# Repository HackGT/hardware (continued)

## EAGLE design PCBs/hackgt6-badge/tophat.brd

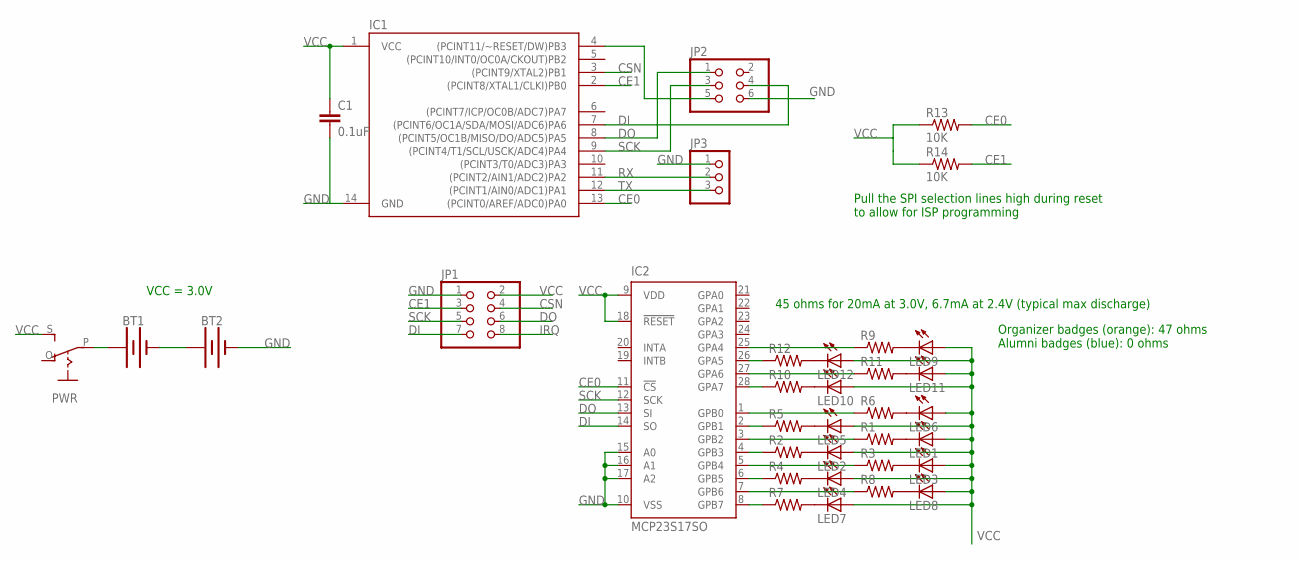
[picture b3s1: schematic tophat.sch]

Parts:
BT1, BT2: BATTERY-AA-SMD
C1: 0.1uF; C1206
IC1: ATTINY84; SO14
IC2: MCP23S17SO; SO28W
JP1: PINHD-2X4/90; 2X04/90
JP2: PINHD-2X3; 2X03
JP3: PINHD-1X3; 1X03
LED1, LED2, LED3, LED4, LED5, LED6, LED7, LED8, LED9, LED10, LED11, LED12: LEDSMT1206; 1206
PWR: EG1218S; EG1218
R1, R2, R3, R4, R5, R6, R7, R8, R9, R10, R11, R12: R-US_R1206; R1206
R13, R14: 10K; R1206

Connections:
CE0: IC1.13 ((PCINT0/AREF/ADC0)PA0), IC2.11 (!CS), R13.2
CE1: IC1.2 ((PCINT8/XTAL1/CLKI)PB0), JP1.3, R14.2
CSN: IC1.3 ((PCINT9/XTAL2)PB1), JP1.4
DI: IC1.7 ((PCINT6/OC1A/SDA/MOSI/ADC6)PA6), IC2.14 (SO), JP1.7, JP2.4
DO: IC1.8 ((PCINT5/OC1B/MISO/DO/ADC5)PA5), IC2.13 (SI), JP1.6, JP2.1
GND: BT2.P$2 (-), BT2.P$4 (-), C1.2, IC1.14 (GND), IC2.10 (VSS), IC2.15 (A0), IC2.16 (A1), IC2.17 (A2), JP1.1, JP2.6, JP3.1
IRQ: JP1.8
unnamed: BT1.P$2 (-), BT1.P$4 (-), BT2.P$1 (+), BT2.P$3 (+)
unnamed: BT1.P$1 (+), BT1.P$3 (+), PWR.P
unnamed: IC2.28 (GPA7), R10.1
unnamed: IC2.27 (GPA6), R11.1
unnamed: LED1.C, R1.2
unnamed: LED2.C, R2.2
unnamed: LED3.C, R3.2
unnamed: LED4.C, R4.2
unnamed: LED5.C, R5.2
unnamed: LED6.C, R6.2
unnamed: LED7.C, R7.2
unnamed: LED8.C, R8.2
unnamed: IC2.26 (GPA5), R12.1
unnamed: IC2.25 (GPA4), R9.1
unnamed: IC2.8 (GPB7), R7.1
unnamed: IC2.1 (GPB0), R6.1
unnamed: IC2.2 (GPB1), R5.1
unnamed: IC2.3 (GPB2), R1.1
unnamed: IC2.4 (GPB3), R2.1
unnamed: IC2.5 (GPB4), R3.1
unnamed: IC2.6 (GPB5), R4.1
unnamed: IC2.7 (GPB6), R8.1
unnamed: LED9.C, R9.2
unnamed: LED10.C, R10.2
unnamed: LED11.C, R11.2
unnamed: LED12.C, R12.2
RST: IC1.4 ((PCINT11/~RESET/DW)PB3), JP2.5
RX: IC1.11 ((PCINT2/AIN1/ADC2)PA2), JP3.2
SCK: IC1.9 ((PCINT4/T1/SCL/USCK/ADC4)PA4), IC2.12 (SCK), JP1.5, JP2.3
TX: IC1.12 ((PCINT1/AIN0/ADC1)PA1), JP3.3
VCC: C1.1, IC1.1 (VCC), IC2.9 (VDD), IC2.18 (!RESET), JP1.2, LED1.A, LED2.A, LED3.A, LED4.A, LED5.A, LED6.A, LED7.A, LED8.A, LED9.A, LED10.A, LED11.A, LED12.A, PWR.S, R13.1, R14.1

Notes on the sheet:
VCC = 3.0V
45 ohms for 20mA at 3.0V, 6.7mA at 2.4V (typical max discharge)
Organizer badges (orange): 47 ohms Alumni badges (blue): 0 ohms
Pull the SPI selection lines high during reset to allow for ISP programming

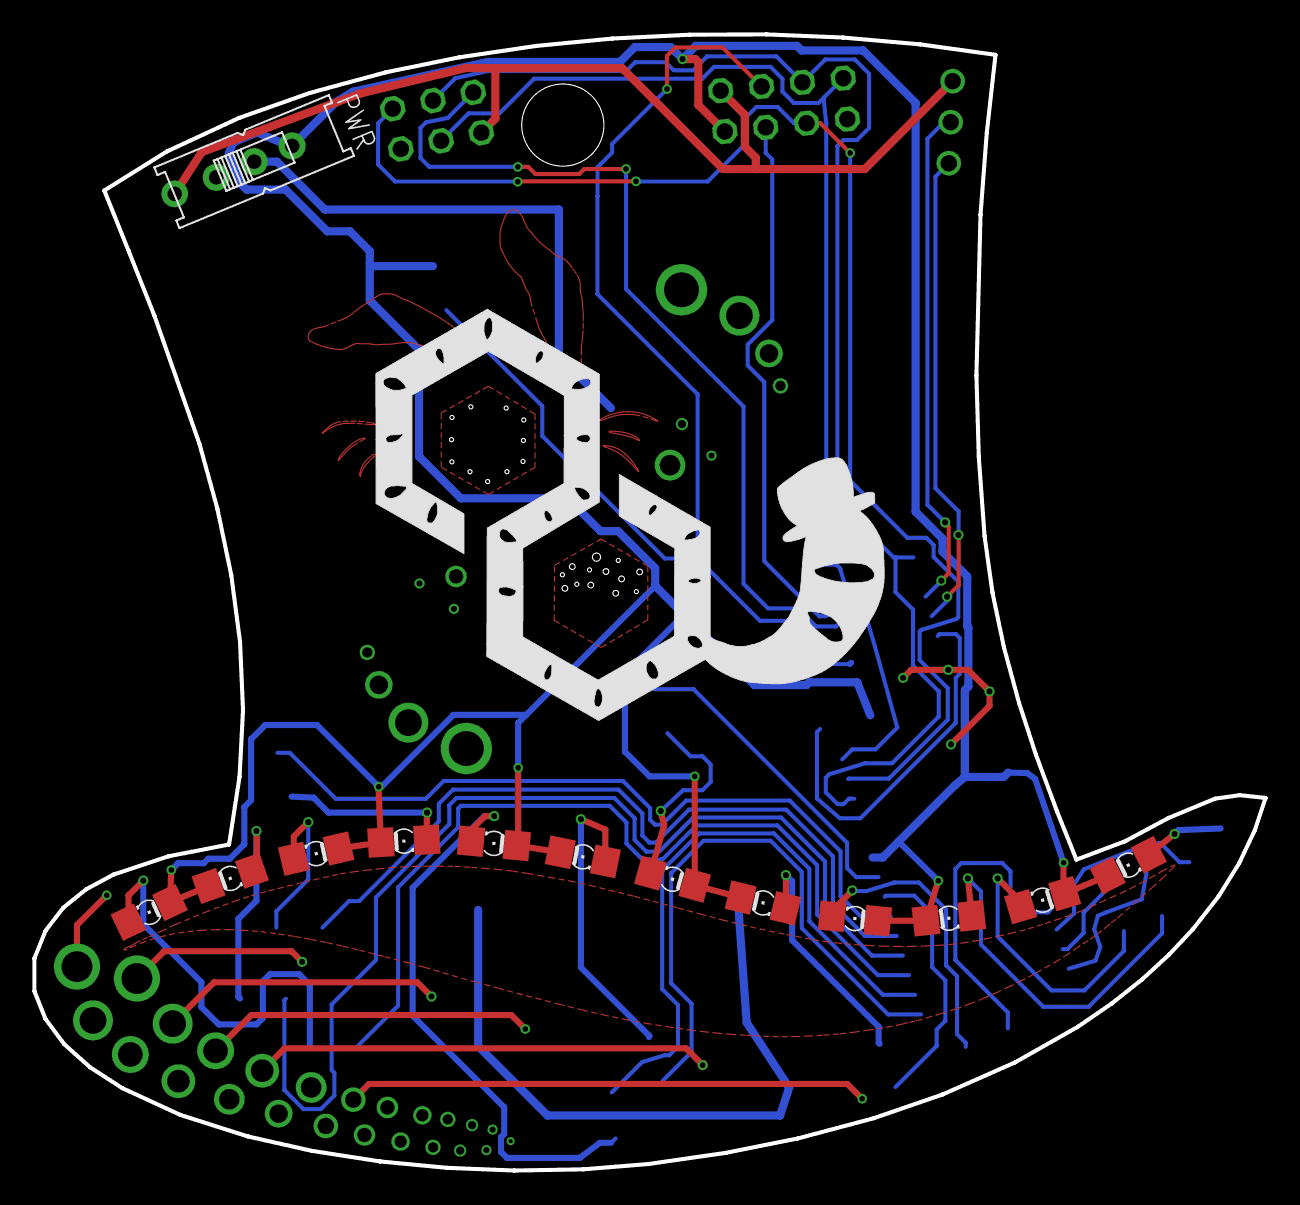
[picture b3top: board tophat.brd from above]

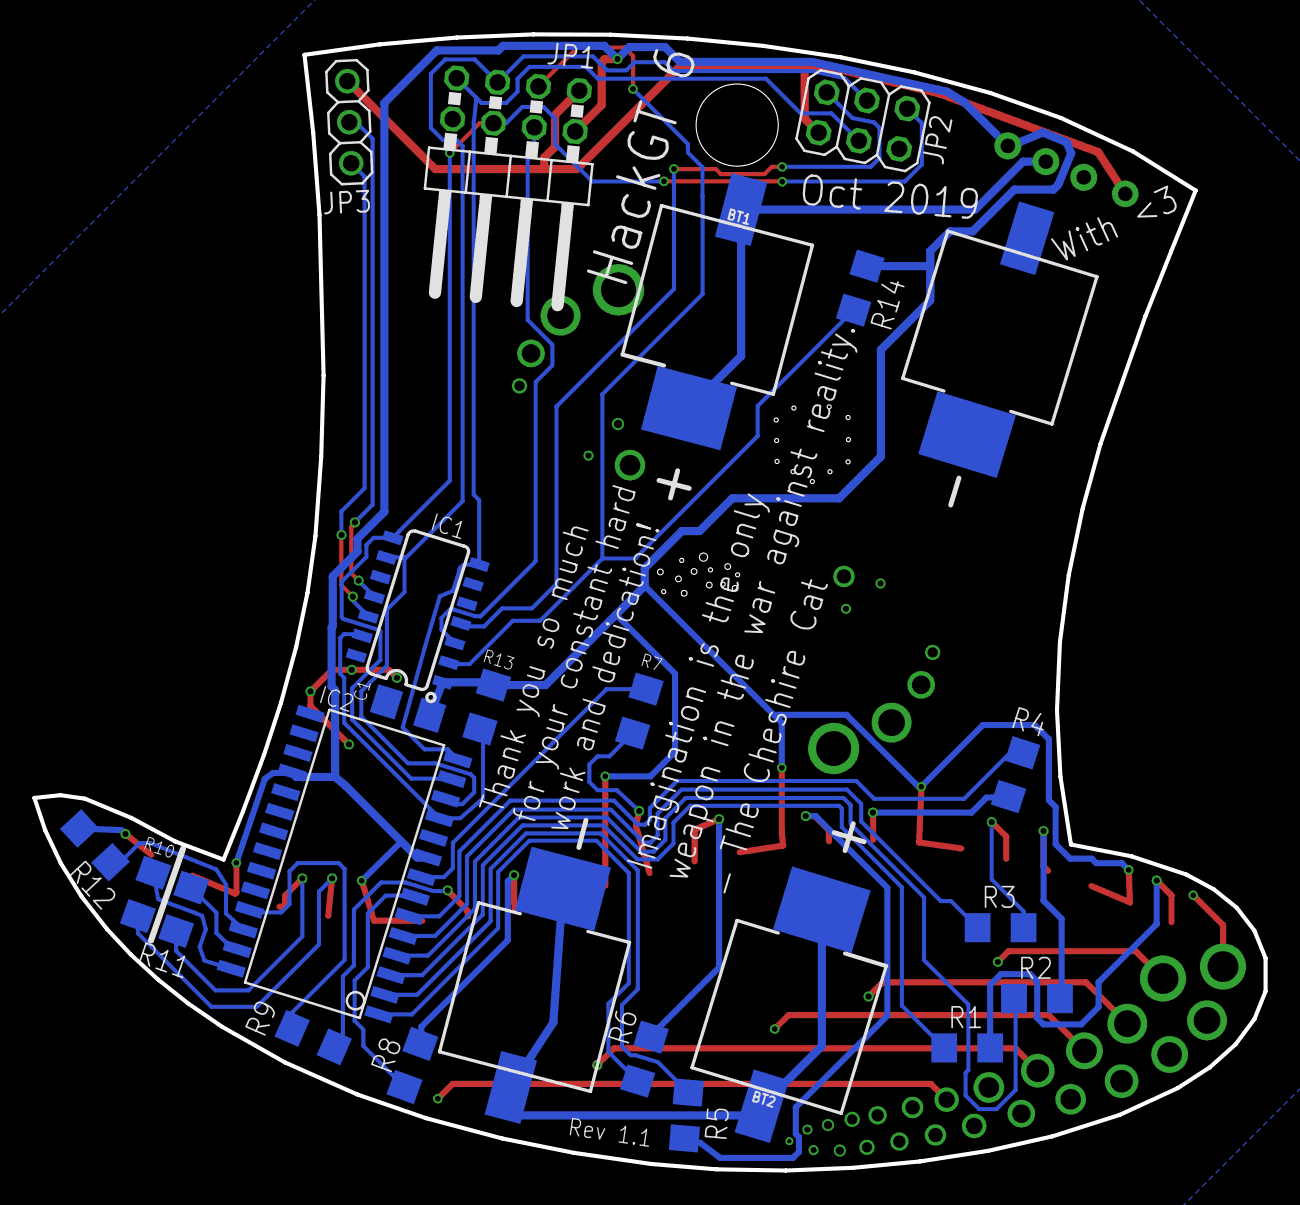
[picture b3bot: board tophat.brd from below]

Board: 2 copper layers, 76.1 x 70.3 mm, 35 parts (22 on the bottom side), 37 nets.

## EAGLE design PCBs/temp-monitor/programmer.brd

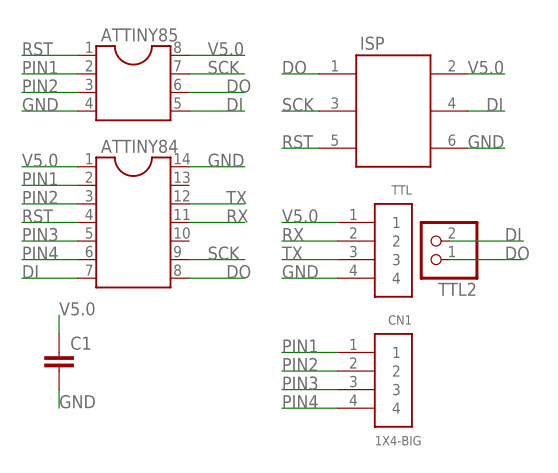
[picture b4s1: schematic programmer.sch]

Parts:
ATTINY84: DIL14S; SOCKET-14
ATTINY85: DIL8S; SOCKET-08
C1: C-EU025-025X050; C025-025X050
CN1: 1X4-BIG; 1X04-BIG
ISP: 61200621621
TTL: 1X4-BIG; 1X04-BIG
TTL2: PINHD-1X2; 1X02

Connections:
DI: ATTINY84.7, ATTINY85.5, ISP.4, TTL2.2
DO: ATTINY84.8, ATTINY85.6, ISP.1, TTL2.1
GND: ATTINY84.14, ATTINY85.4, C1.2, ISP.6, TTL.4
PIN1: ATTINY84.2, ATTINY85.2, CN1.1
PIN2: ATTINY84.3, ATTINY85.3, CN1.2
PIN3: ATTINY84.5, CN1.3
PIN4: ATTINY84.6, CN1.4
RST: ATTINY84.4, ATTINY85.1, ISP.5
RX: ATTINY84.11, TTL.2
SCK: ATTINY84.9, ATTINY85.7, ISP.3
TX: ATTINY84.12, TTL.3
V5.0: ATTINY84.1, ATTINY85.8, C1.1, ISP.2, TTL.1

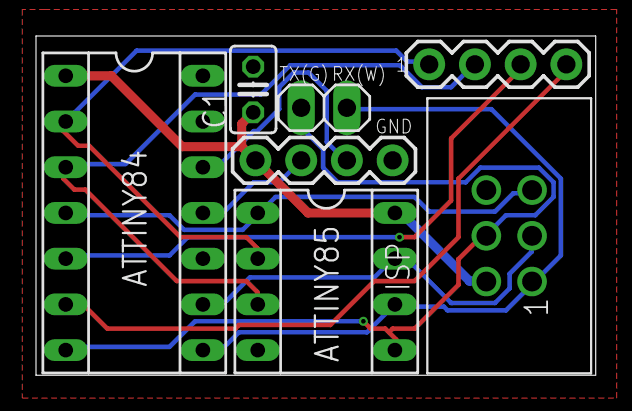
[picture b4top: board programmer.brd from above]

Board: 2 copper layers, 31.1 x 18.8 mm, 7 parts (0 on the bottom side), 12 nets.

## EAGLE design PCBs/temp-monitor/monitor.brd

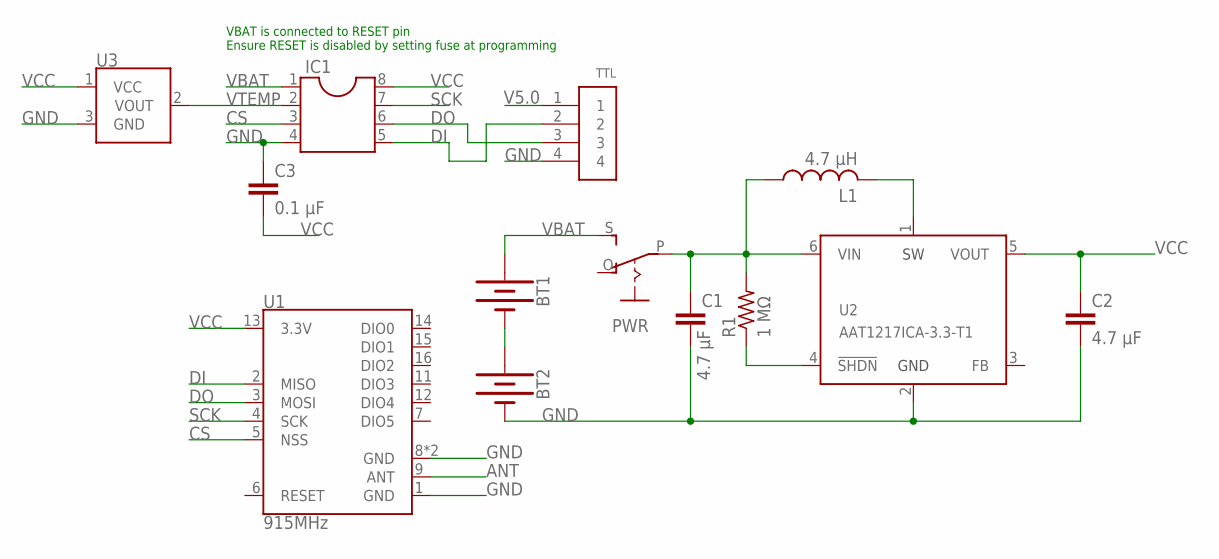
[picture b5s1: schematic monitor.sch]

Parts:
BT1, BT2: BATTERY-AA
C1, C2: 4.7 µF; C025-025X050
C3: 0.1 µF; C025-025X050
IC1: DIL8S; SOCKET-08
L1: 4.7 µH; 0207/12
PWR: EG1218S; EG1218
R1: 1 MΩ; 0204/5
TTL: 1X4-BIG; 1X04-BIG
U1: 915MHz; RFM69HCW-XXXS2
U2: AAT1217ICA-3.3-T1; TSOT-23-6
U3: TMP36GT9; TO-92

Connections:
ANT: U1.9 (ANT)
CS: IC1.3, U1.5 (NSS)
DI: IC1.5, TTL.2, U1.2 (MISO)
DO: IC1.6, TTL.3, U1.3 (MOSI)
GND: BT2.GND@1 (-), C1.2, C2.2, C3.1, IC1.4, TTL.4, U1.1 (GND), U1.8 (GND), U1.10 (GND), U2.2 (GND), U3.3 (GND)
unnamed: BT1.GND@1 (-), BT2.PWR@1 (+)
unnamed: BT1.PWR@1 (+), PWR.S
SCK: IC1.7, U1.4 (SCK)
SHDN: R1.1, U2.4 (!SHDN)
SW: L1.2, U2.1 (SW)
V5.0: TTL.1
VBAT: C1.1, IC1.1, L1.1, PWR.P, R1.2, U2.6 (VIN)
VCC: C2.1, C3.2, IC1.8, U1.13 (3.3V), U2.5 (VOUT), U3.1 (VCC)
VTEMP: IC1.2, U3.2 (VOUT)

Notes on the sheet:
VBAT is connected to RESET pin Ensure RESET is disabled by setting fuse at programming

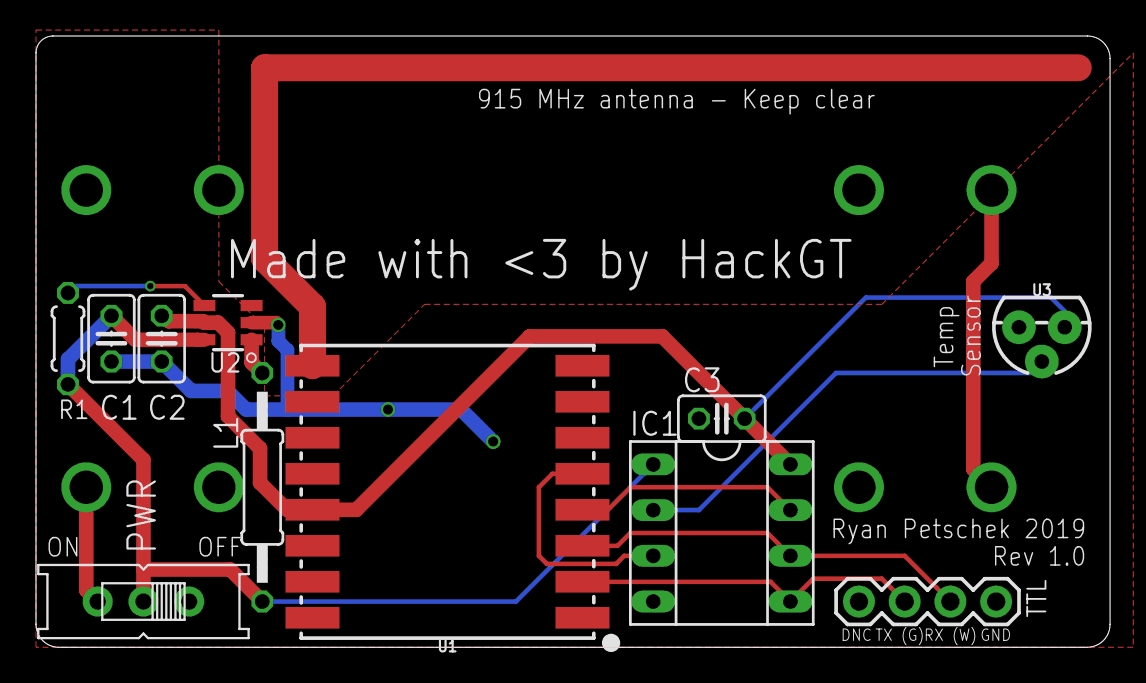
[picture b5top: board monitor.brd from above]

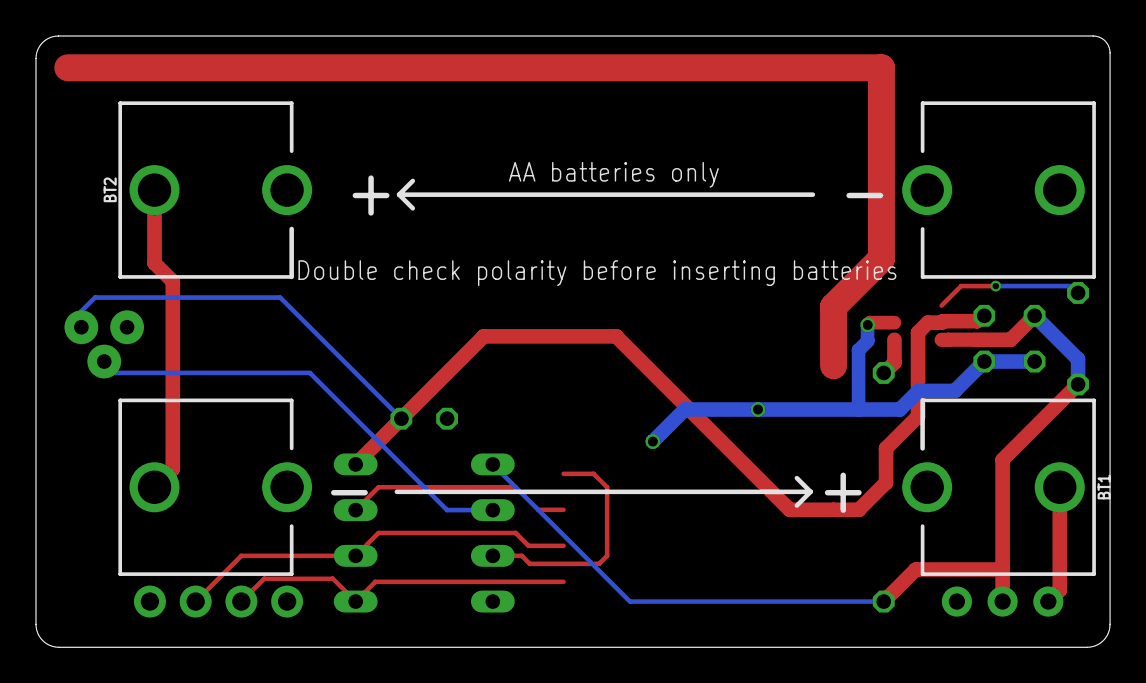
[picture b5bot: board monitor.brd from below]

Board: 2 copper layers, 59.7 x 34.0 mm, 13 parts (2 on the bottom side), 12 nets.

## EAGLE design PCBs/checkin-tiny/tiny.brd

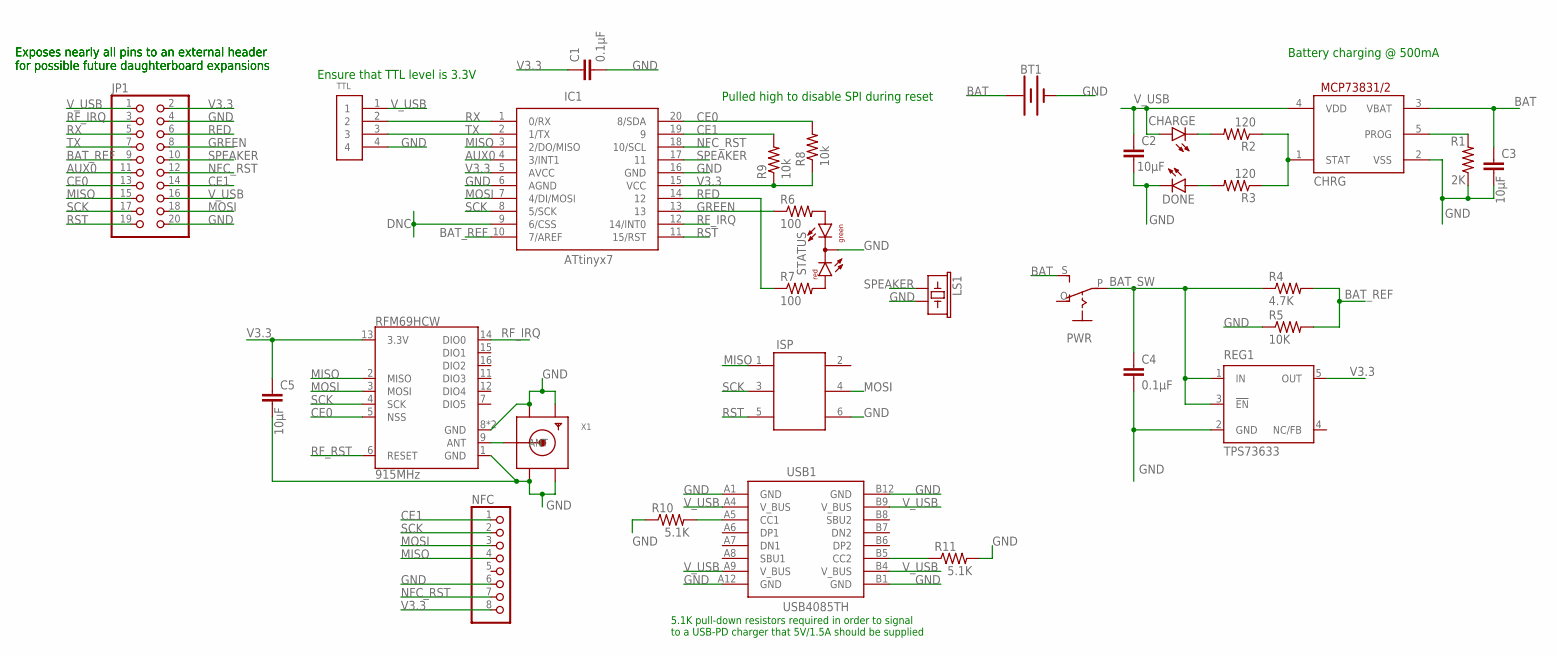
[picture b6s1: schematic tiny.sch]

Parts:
BT1: BATTERY-18650; BATTERY_18650-HOLDER
C1, C4: 0.1µF; C025-025X050
C2, C3: 10µF; C050-030X075
C5: 10µF; C025-025X050
CHARGE: LED3MM
CHRG: MCP73831/OT; SOT23-5L
DONE: LED3MM
IC1: ATtinyx7; SOIC127P1030X265-20N
ISP: 61200621621
JP1: PINHD-2X10; 2X10
LS1: Buzz Buzz; BUZZER-12MM
NFC: PINHD-1X8BIG; 1X08-BIG
PWR: EG1218S; EG1218
R1: 2K; 0204/5
R2, R3: 120; 0204/5
R4: 4.7K; 0204/5
R5: 10K; 0204/5
R6, R7: 100; 0204/5
R8, R9: 10k; 0204/5
R10, R11: 5.1K; 0204/5
REG1: TPS73633; SOT23-DBV
RFM69HCW: 915MHz; RFM69HCW-XXXS2
STATUS: DUOLED-RG-C; DUOLED-C-5MM
TTL: 1X4-BIG; 1X04-BIG
USB1: USB4085TH; USB4085
X1: SMACONNECTOR_EDGE; SMA_EDGELAUNCH

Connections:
ANT: RFM69HCW.9 (ANT), X1.P (ANT)
AUX0: IC1.4 (3/INT1), JP1.11
BAT: BT1.PWR@1 (+), BT1.PWR@2 (+), BT1.PWR@3 (+), C3.1, CHRG.3 (VBAT), PWR.S
BAT_REF: IC1.10 (7/AREF), JP1.9, R4.2, R5.2
BAT_SW: C4.1, PWR.P, R4.1, REG1.1 (IN), REG1.3 (!EN)
CE0: IC1.20 (8/SDA), JP1.13, R8.2, RFM69HCW.5 (NSS)
CE1: IC1.19 (9), JP1.14, NFC.1, R9.2
DNC: IC1.9 (6/CSS)
GND: BT1.GND@1 (-), BT1.GND@2 (-), BT1.GND@3 (-), C1.2, C2.2, C3.2, C4.2, C5.2, CHRG.2 (VSS), DONE.K (C), IC1.6 (AGND), IC1.16 (GND), ISP.6, JP1.4, JP1.20, LS1.- (2), NFC.6, R1.1, R5.1, R10.1, R11.2, REG1.2 (GND), RFM69HCW.1 (GND), RFM69HCW.8 (GND), RFM69HCW.10 (GND), STATUS.C, TTL.4, USB1.A1 (GND), USB1.A12 (GND), USB1.B1 (GND), USB1.B12 (GND), X1.GND@1 (GND4), X1.GND@2 (GND3), X1.GND@3 (GND2), X1.GND@4 (GND1)
GREEN: IC1.13, JP1.8, R6.1
MISO: IC1.3 (2/DO/MISO), ISP.1, JP1.15, NFC.4, RFM69HCW.2 (MISO)
MOSI: IC1.7 (4/DI/MOSI), ISP.4, JP1.18, NFC.3, RFM69HCW.3 (MOSI)
unnamed: DONE.A, R3.2
unnamed: CHRG.1 (STAT), R2.1, R3.1
unnamed: R6.2, STATUS.AX (AG)
unnamed: R10.2, USB1.A5 (CC1)
unnamed: R11.1, USB1.B5 (CC2)
unnamed: CHARGE.K (C), R2.2
unnamed: CHRG.5 (PROG), R1.2
unnamed: R7.2, STATUS.AR
NFC_RST: IC1.18 (10/SCL), JP1.12, NFC.7
RED: IC1.14 (12), JP1.6, R7.1
RF_IRQ: IC1.12 (14/INT0), JP1.3, RFM69HCW.14 (DIO0)
RF_RST: RFM69HCW.6 (RESET)
RST: IC1.11 (15/RST), ISP.5, JP1.19
RX: IC1.1 (0/RX), JP1.5, TTL.2
SCK: IC1.8 (5/SCK), ISP.3, JP1.17, NFC.2, RFM69HCW.4 (SCK)
SPEAKER: IC1.17 (11), JP1.10, LS1.+ (1)
TX: IC1.2 (1/TX), JP1.7, TTL.3
V3.3: C1.1, C5.1, IC1.5 (AVCC), IC1.15 (VCC), JP1.2, NFC.8, R8.1, R9.1, REG1.5 (OUT), RFM69HCW.13 (3.3V)
V_USB: C2.1, CHARGE.A, CHRG.4 (VDD), JP1.1, JP1.16, TTL.1, USB1.A4 (V_BUS), USB1.A9 (V_BUS), USB1.B4 (V_BUS), USB1.B9 (V_BUS)

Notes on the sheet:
Pulled high to disable SPI during reset
Battery charging @ 500mA
5.1K pull-down resistors required in order to signal to a USB-PD charger that 5V/1.5A should be supplied
Exposes nearly all pins to an external header for possible future daughterboard expansions
Ensure that TTL level is 3.3V

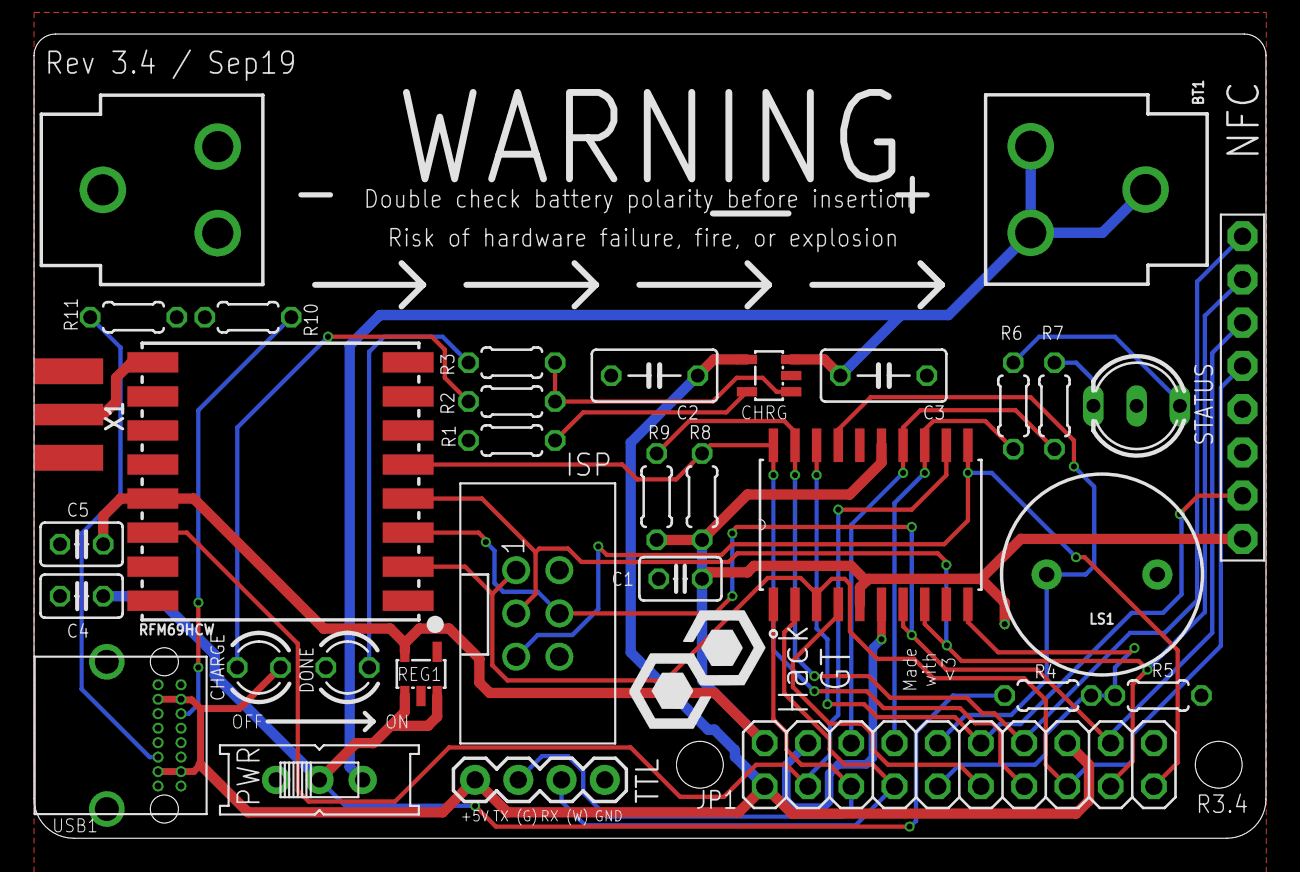
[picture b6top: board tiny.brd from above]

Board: 2 copper layers, 72.4 x 47.2 mm, 32 parts (0 on the bottom side), 29 nets.

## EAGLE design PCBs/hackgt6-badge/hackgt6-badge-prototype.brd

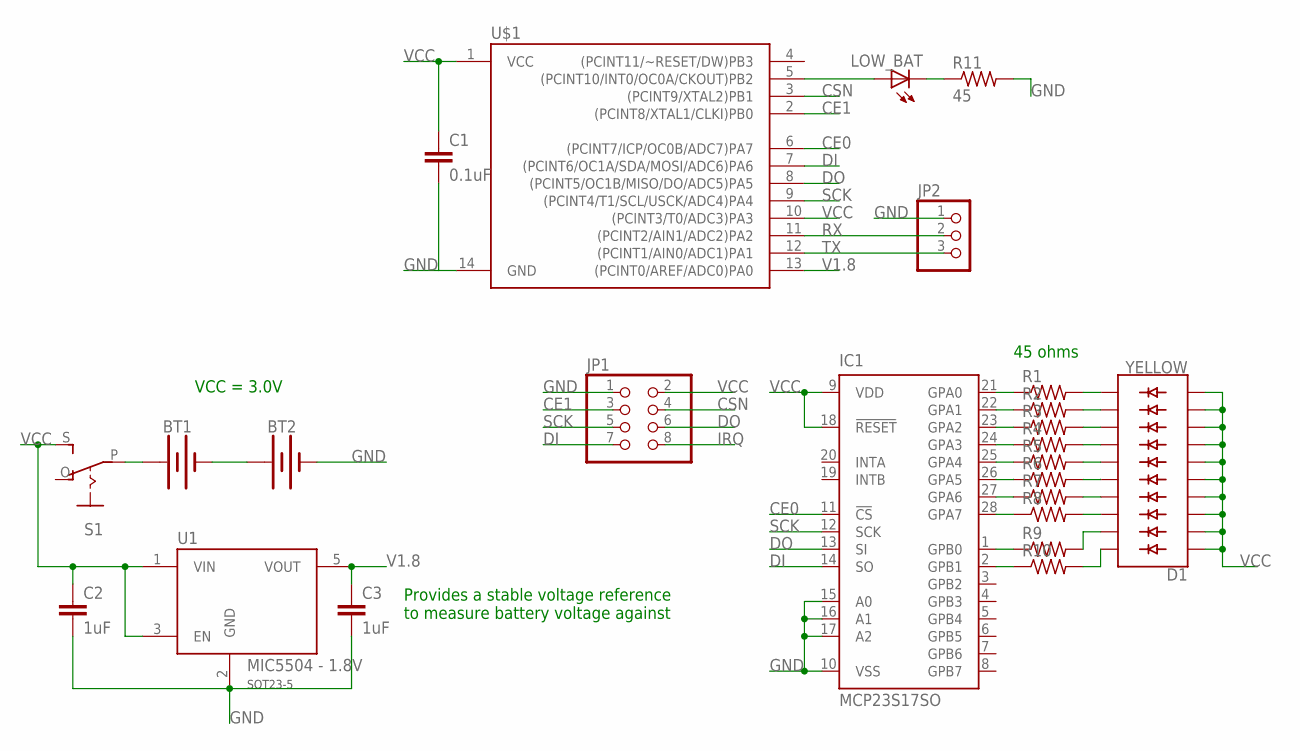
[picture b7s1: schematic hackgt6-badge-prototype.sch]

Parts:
BT1, BT2: BATTERY-AA-SMD
C1: 0.1uF; C1206
C2, C3: 1uF; C1206
D1: YELLOW; LED_BARGRAPH_10
IC1: MCP23S17SO; SO28W
JP1: PINHD-2X4/90; 2X04/90
JP2: PINHD-1X3; 1X03
LOW_BAT: LEDCHIPLED_1206; CHIPLED_1206
R1, R2, R3, R4, R5, R6, R7, R8, R9, R10: R-US_R1206; R1206
R11: 45; R1206
S1: EG1218S; EG1218
U1: MIC5504 - 1.8V; SOT23-5-DBV
U$1: ATTINY84ATTINY84-20PU; DIP14

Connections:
CE0: IC1.11 (!CS), U$1.6 ((PCINT7/ICP/OC0B/ADC7)PA7)
CE1: JP1.3, U$1.2 ((PCINT8/XTAL1/CLKI)PB0)
CSN: JP1.4, U$1.3 ((PCINT9/XTAL2)PB1)
DI: IC1.14 (SO), JP1.7, U$1.7 ((PCINT6/OC1A/SDA/MOSI/ADC6)PA6)
DO: IC1.13 (SI), JP1.6, U$1.8 ((PCINT5/OC1B/MISO/DO/ADC5)PA5)
GND: BT2.P$2 (-), BT2.P$4 (-), C1.2, C2.2, C3.2, IC1.10 (VSS), IC1.15 (A0), IC1.16 (A1), IC1.17 (A2), JP1.1, JP2.1, R11.2, U1.2 (GND), U$1.14 (GND)
IRQ: JP1.8
unnamed: BT1.P$2 (-), BT1.P$4 (-), BT2.P$1 (+), BT2.P$3 (+)
unnamed: BT1.P$1 (+), BT1.P$3 (+), S1.P
unnamed: IC1.21 (GPA0), R1.1
unnamed: LOW_BAT.A, U$1.5 ((PCINT10/INT0/OC0A/CKOUT)PB2)
unnamed: IC1.22 (GPA1), R2.1
unnamed: D1.11 (C9), R1.2
unnamed: D1.12 (C8), R2.2
unnamed: D1.13 (C7), R3.2
unnamed: D1.14 (C6), R4.2
unnamed: D1.15 (C5), R5.2
unnamed: D1.16 (C4), R6.2
unnamed: D1.17 (C3), R7.2
unnamed: D1.18 (C2), R8.2
unnamed: D1.19 (C1), R9.2
unnamed: D1.20 (C), R10.2
unnamed: IC1.1 (GPB0), R9.1
unnamed: IC1.2 (GPB1), R10.1
unnamed: IC1.28 (GPA7), R8.1
unnamed: IC1.27 (GPA6), R7.1
unnamed: IC1.26 (GPA5), R6.1
unnamed: IC1.25 (GPA4), R5.1
unnamed: IC1.24 (GPA3), R4.1
unnamed: IC1.23 (GPA2), R3.1
unnamed: LOW_BAT.C, R11.1
RX: JP2.2, U$1.11 ((PCINT2/AIN1/ADC2)PA2)
SCK: IC1.12 (SCK), JP1.5, U$1.9 ((PCINT4/T1/SCL/USCK/ADC4)PA4)
TX: JP2.3, U$1.12 ((PCINT1/AIN0/ADC1)PA1)
V1.8: C3.1, U1.5 (VOUT), U$1.13 ((PCINT0/AREF/ADC0)PA0)
VCC: C1.1, C2.1, D1.1 (A), D1.2 (A1), D1.3 (A2), D1.4 (A3), D1.5 (A4), D1.6 (A5), D1.7 (A6), D1.8 (A7), D1.9 (A8), D1.10 (A9), IC1.9 (VDD), IC1.18 (!RESET), JP1.2, S1.S, U1.1 (VIN), U1.3 (EN), U$1.1 (VCC), U$1.10 ((PCINT3/T0/ADC3)PA3)

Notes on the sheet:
Provides a stable voltage reference to measure battery voltage against
45 ohms
VCC = 3.0V

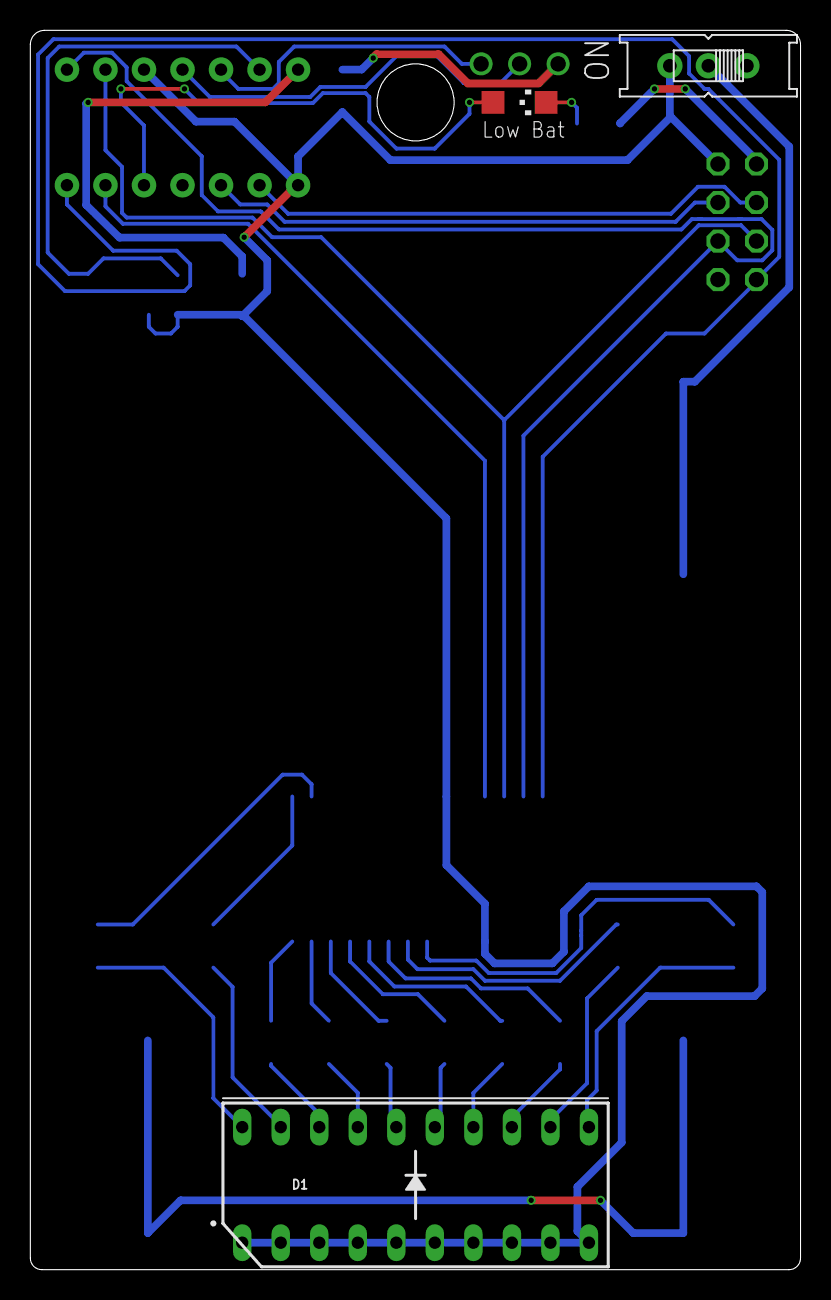
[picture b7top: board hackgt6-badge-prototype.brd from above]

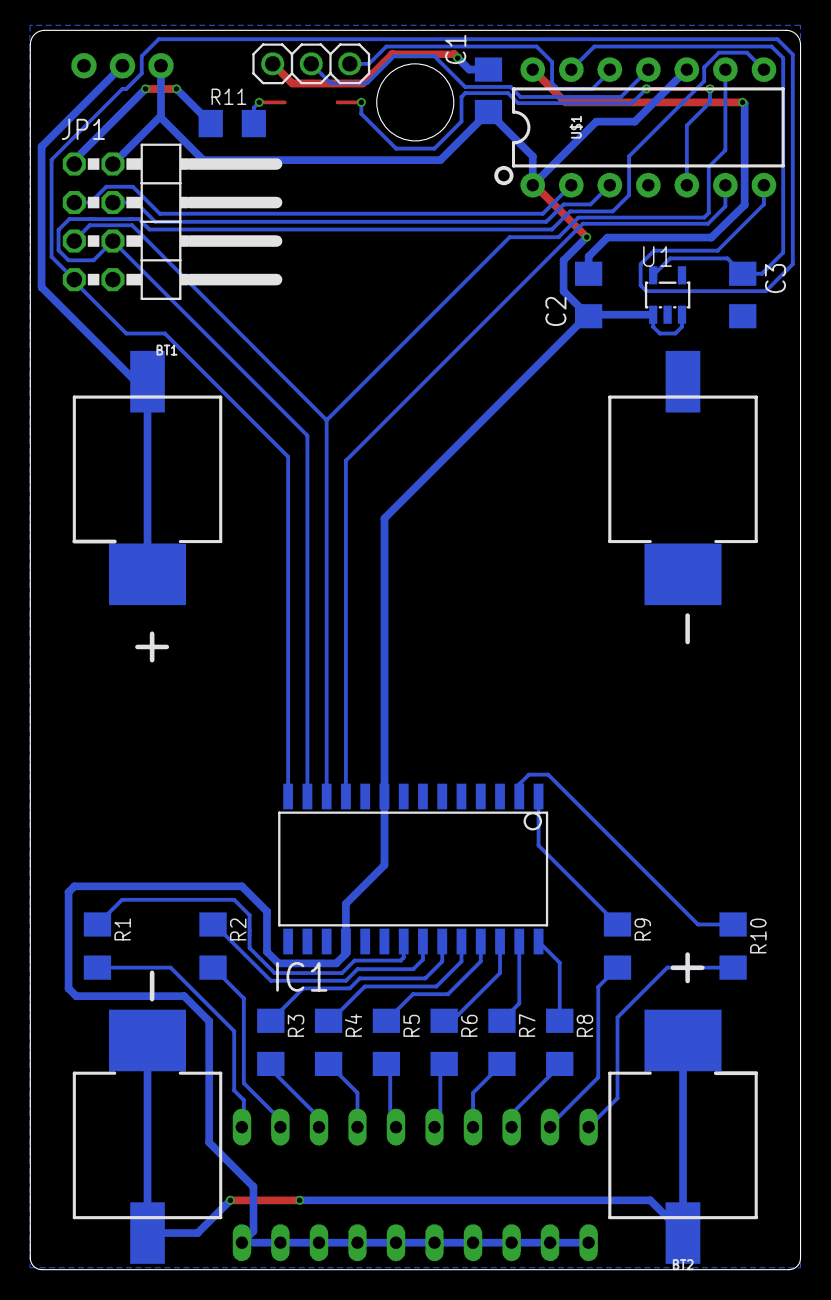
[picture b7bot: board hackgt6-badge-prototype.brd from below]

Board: 2 copper layers, 50.8 x 81.7 mm, 24 parts (21 on the bottom side), 35 nets.

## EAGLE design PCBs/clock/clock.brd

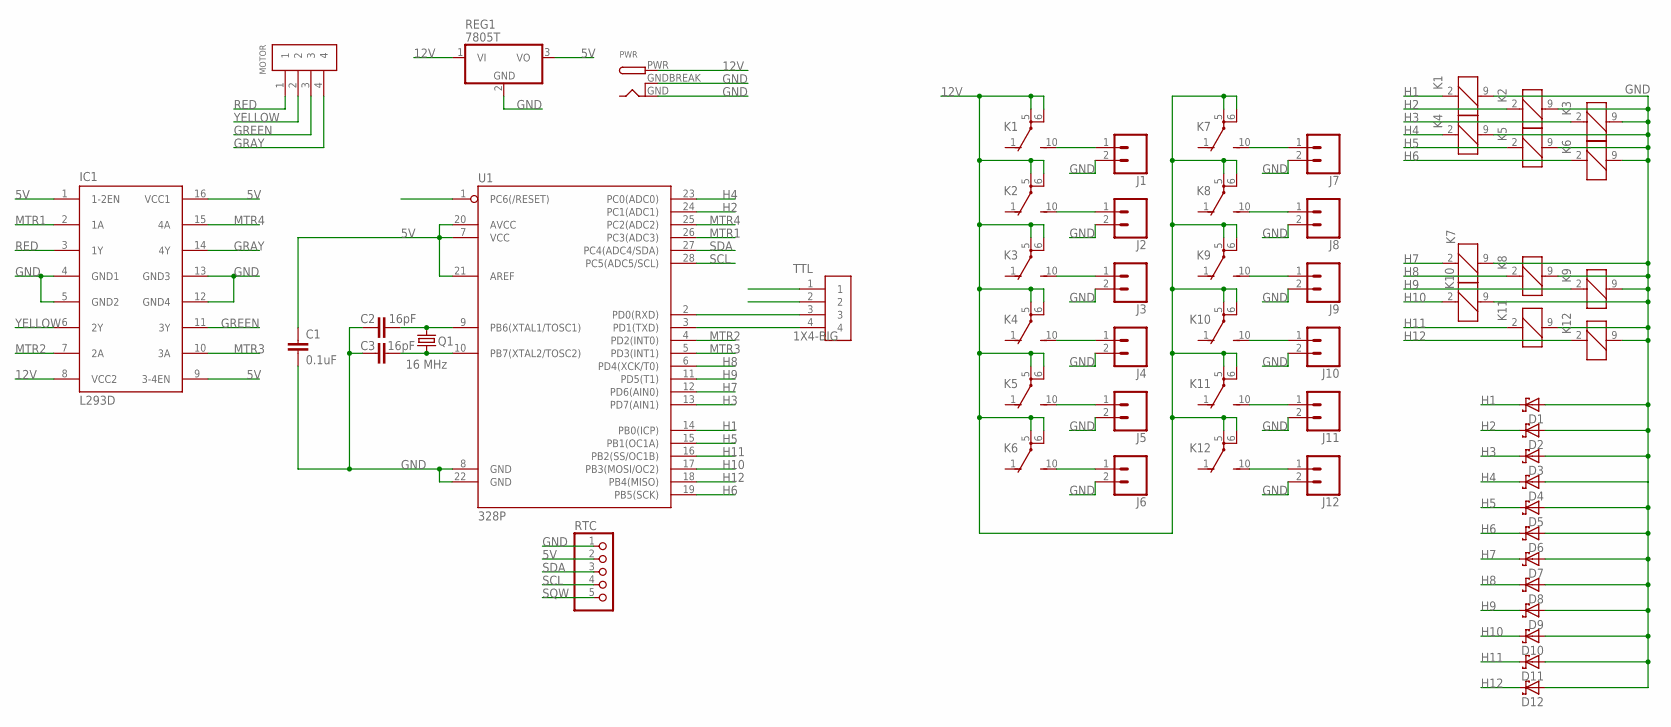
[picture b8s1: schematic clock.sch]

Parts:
C1: 0.1uF; C1206
C2, C3: 16pF; C0805
D1, D2, D3, D4, D5, D6, D7, D8, D9, D10, D11, D12: SCHOTTKY-DIODEDO41-7; DO41-7
IC1: L293D; DIL16
J1, J2, J3, J4, J5, J6, J7, J8, J9, J10, J11, J12: CONN_02; 1X02
K1, K2, K3, K4, K5, K6, K7, K8, K9, K10, K11, K12: G5V1
MOTOR: 1X4-BIG; 1X04-BIG
PWR: DCBARRELPTH; DCJACK_2MM_PTH
Q1: 16 MHz; HC49/S
REG1: 7805T; TO220H
RTC: PINHD-1X5; 1X05
TTL: 1X4-BIG; 1X04-BIG
U1: 328P; DIP28

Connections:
5V: C1.1, IC1.1 (1-2EN), IC1.9 (3-4EN), IC1.16 (VCC1), REG1.3 (VO), RTC.2, U1.7 (VCC), U1.20 (AVCC), U1.21 (AREF)
12V: IC1.8 (VCC2), K1.5, K1.6, K2.5, K2.6, K3.5, K3.6, K4.5, K4.6, K5.5, K5.6, K6.5, K6.6, K7.5, K7.6, K8.5, K8.6, K9.5, K9.6, K10.5, K10.6, K11.5, K11.6, K12.5, K12.6, PWR.PWR, REG1.1 (VI)
GND: C1.2, C2.1, C3.1, D1.A, D2.A, D3.A, D4.A, D5.A, D6.A, D7.A, D8.A, D9.A, D10.A, D11.A, D12.A, IC1.4 (GND1), IC1.5 (GND2), IC1.12 (GND4), IC1.13 (GND3), J1.2, J2.2, J3.2, J4.2, J5.2, J6.2, J7.2, J8.2, J9.2, J10.2, J11.2, J12.2, K1.9 (2), K2.9 (2), K3.9 (2), K4.9 (2), K5.9 (2), K6.9 (2), K7.9 (2), K8.9 (2), K9.9 (2), K10.9 (2), K11.9 (2), K12.9 (2), PWR.GND, PWR.GNDBREAK, REG1.2 (GND), RTC.1, U1.8 (GND), U1.22 (GND)
GRAY: IC1.14 (4Y), MOTOR.4
GREEN: IC1.11 (3Y), MOTOR.3
H1: D1.C, K1.2 (1), U1.14 (PB0(ICP))
H2: D2.C, K2.2 (1), U1.24 (PC1(ADC1))
H3: D3.C, K3.2 (1), U1.13 (PD7(AIN1))
H4: D4.C, K4.2 (1), U1.23 (PC0(ADC0))
H5: D5.C, K5.2 (1), U1.15 (PB1(OC1A))
H6: D6.C, K6.2 (1), U1.19 (PB5(SCK))
H7: D7.C, K7.2 (1), U1.12 (PD6(AIN0))
H8: D8.C, K8.2 (1), U1.6 (PD4(XCK/T0))
H9: D9.C, K9.2 (1), U1.11 (PD5(T1))
H10: D10.C, K10.2 (1), U1.17 (PB3(MOSI/OC2))
H11: D11.C, K11.2 (1), U1.16 (PB2(SS/OC1B))
H12: D12.C, K12.2 (1), U1.18 (PB4(MISO))
MTR1: IC1.2 (1A), U1.26 (PC3(ADC3))
MTR2: IC1.7 (2A), U1.4 (PD2(INT0))
MTR3: IC1.10 (3A), U1.5 (PD3(INT1))
MTR4: IC1.15 (4A), U1.25 (PC2(ADC2))
unnamed: J1.1, K1.10 (S)
unnamed: J2.1, K2.10 (S)
unnamed: J3.1, K3.10 (S)
unnamed: J4.1, K4.10 (S)
unnamed: J5.1, K5.10 (S)
unnamed: J6.1, K6.10 (S)
unnamed: J7.1, K7.10 (S)
unnamed: J8.1, K8.10 (S)
unnamed: J9.1, K9.10 (S)
unnamed: J10.1, K10.10 (S)
unnamed: J11.1, K11.10 (S)
unnamed: J12.1, K12.10 (S)
unnamed: C2.2, Q1.2, U1.9 (PB6(XTAL1/TOSC1))
unnamed: C3.2, Q1.1, U1.10 (PB7(XTAL2/TOSC2))
unnamed: TTL.3, U1.2 (PD0(RXD))
unnamed: TTL.4, U1.3 (PD1(TXD))
RED: IC1.3 (1Y), MOTOR.1
SCL: RTC.4, U1.28 (PC5(ADC5/SCL))
SDA: RTC.3, U1.27 (PC4(ADC4/SDA))
SQW: RTC.5
YELLOW: IC1.6 (2Y), MOTOR.2

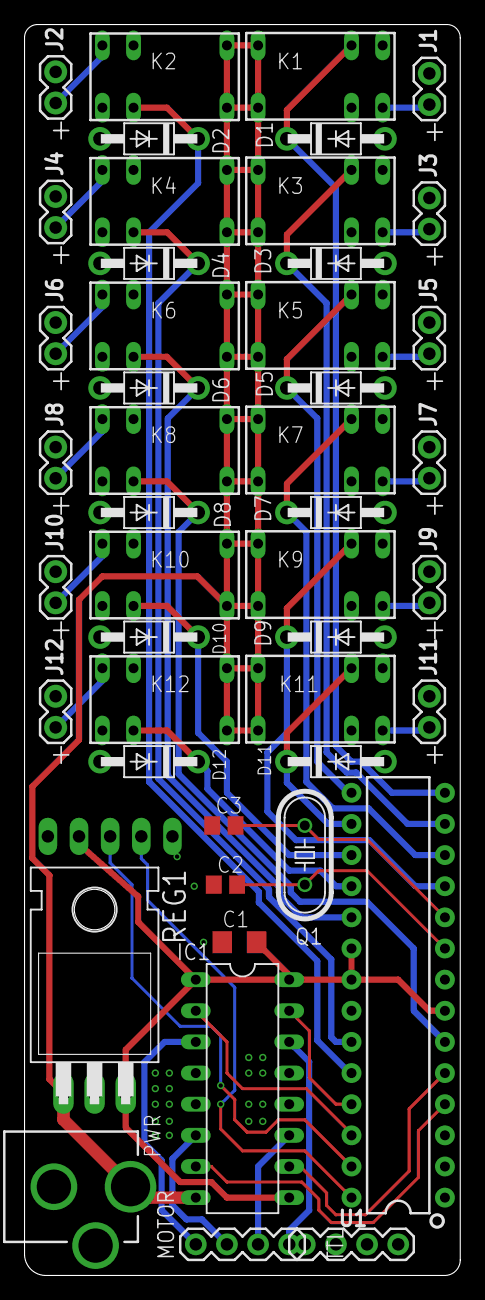
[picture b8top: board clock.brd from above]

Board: 2 copper layers, 35.5 x 102.0 mm, 47 parts (1 on the bottom side), 41 nets.

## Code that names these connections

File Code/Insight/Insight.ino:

#include <SPI.h>
#include <RFM69registers.h>
#include <RFM69.h>
#include "MFRC522.h"

#define RED 12
#define GREEN 13
#define BUZZER 11
#define BAT_REF A7
#define NFC_RST_PIN 10
#define NFC_SS_PIN 9
#define RF_SS_PIN 8
#define RF_IRQ_PIN 14

#define ENCRYPT_KEY "HackGT 6: Rabbit" // Must be 16 bytes long
#define BASE_STATION_ID 0
#define NETWORK_ID 6 // HackGT 6 haha
#define RETRY_COUNT 3
#define ACK_TIMEOUT 50 // ms

// IMPORTANT: Set this to the ID of the label on the board
#define BOARD_ID 1

// Enables Serial debugging output
// Do not enable in production in order to reduce compiled output size
//#define DEBUG

MFRC522 mfrc522(NFC_SS_PIN, NFC_RST_PIN);
RFM69 radio(RF_SS_PIN, RF_IRQ_PIN);

enum MessageType {
	Heartbeat,
	BatteryLevel,
	Scan,
  PuzzleCompletion
};
typedef struct {
	enum MessageType type;
	byte payload[36]; // Max 36 byte payload (UUID size)
} Message;

void setup() {
    pinMode(RED, OUTPUT);
    pinMode(GREEN, OUTPUT);
    pinMode(BUZZER, OUTPUT);
    pinMode(BAT_REF, INPUT);
    pinMode(NFC_RST_PIN, OUTPUT);
    pinMode(NFC_SS_PIN, OUTPUT);

	#ifdef DEBUG
    	Serial.begin(9600);
		Serial.print(F("Board ID is: "));
		Serial.println(BOARD_ID);
	#endif

  SPI.begin();
  mfrc522.PCD_Init();
  delay(50);
//     mfrc522.PCD_SetAntennaGain(mfrc522.RxGain_max);
	#ifdef DEBUG
    	mfrc522.PCD_DumpVersionToSerial();
	#endif

	if (!radio.initialize(RF69_915MHZ, BOARD_ID, NETWORK_ID)) {
		#ifdef DEBUG
			Serial.println(F("Couldn't init() radio"));
		#endif
	}
	// Default baud rate is 55,555 bps
	// Set to 9600 bps for better range
	// This is sufficient for 30 40-byte messages per second
	radio.writeReg(REG_BITRATEMSB, RF_BITRATEMSB_9600);
	radio.writeReg(REG_BITRATELSB, RF_BITRATELSB_9600);
	radio.setHighPower();
	radio.encrypt(ENCRYPT_KEY);

	digitalWrite(GREEN, HIGH);
	digitalWrite(RED, HIGH);
	tone(BUZZER, 300);

	Message message;
	message.type = Heartbeat;
	bool sendSuccess = radio.sendWithRetry(BASE_STATION_ID, (const void*)(&message), sizeof(Message), RETRY_COUNT, ACK_TIMEOUT);
	if (sendSuccess) {
		tone(BUZZER, 1000);
	}
	else {
		tone(BUZZER, 200);
		digitalWrite(GREEN, LOW);
	}
	delay(150);
	noTone(BUZZER);
	digitalWrite(GREEN, LOW);
	digitalWrite(RED, LOW);
}

unsigned long lastBatteryReport = 0;
void loop() {
	radio.sleep();

	handleNFC();

	// Report battery level every ~15 seconds
	if (lastBatteryReport == 0 || millis() - lastBatteryReport >= 15000) {
		reportBatteryLevel();
		lastBatteryReport = millis();
	}
}

void reportBatteryLevel() {
	// 1.47 is the voltage divider ratio
	// 3300 is the reference voltage (3.3 volts)
	// ATtinys have a 10 bit ADC -> divide by 1024
	uint16_t voltage = analogRead(BAT_REF) * 1.47 * 3300 / 1024;

	Message message;
	message.type = BatteryLevel;
	message.payload[0] = voltage & 0xFF; // Lower byte
	message.payload[1] = voltage >> 8; // Upper byte

	#ifdef DEBUG
		Serial.print("Battery voltage: ");
		Serial.println(voltage, DEC);
	#endif

	radio.sendWithRetry(BASE_STATION_ID, (const void*)(&message), sizeof(Message), RETRY_COUNT, ACK_TIMEOUT);
}

void handleNFC() {
	if (!mfrc522.PICC_IsNewCardPresent()) {
		return;
	}
	// Selects one of the cards in the RF field
	if (!mfrc522.PICC_ReadCardSerial()) {
		return;
	}

	/*
	 * We want to read pages 0x04 to 0x14 in order to read the entire used data block off the card
	 *     This is because https://info.hack.gt?user=<uuid> is exactly long enough to end at page 0x14
	 * However, the FIFO buffer used in the MFRC522 has a max capacity of 64 bytes (62 usable after 2 byte response CRC)
	 * Therefore, we read starting at page 0x06 which is partially into the TLV and NDEF data blocks
	 * We just scan until we see the string `?user=` and assume everything after that is the UUID
	 * We stop reading when we reach a byte with value 0xFE since this is the TLV block terminator byte
	 */

	const byte startPage = 0x06;
	const byte endPage = 0x14; // Just long enough for HackGT badge IDs
	byte receiveBufferSize = 62; // Only 62 usable bytes can be returned from the MFRC522 FIFO buffer after 2 byte CRC is removed
	byte receiveBuffer[receiveBufferSize];
	byte result = mfrc522.MIFARE_FastRead(startPage, endPage, (byte*)&receiveBuffer, &receiveBufferSize);
	#ifdef DEBUG
		// hexPrint(receiveBuffer, receiveBufferSize);
	#endif

	Message message;
	message.type = Scan;

	bool isUUIDSection = false;
	const char uuidSeparator[6] = "?user=";
	for (byte i = 0, uuidIndex = 0; i < receiveBufferSize; i++) {
		if (receiveBuffer[i] == 0xFE) break; // TLV terminator
		if (!isUUIDSection
			&& (i + 5) < receiveBufferSize
			&& receiveBuffer[i + 0] == uuidSeparator[0]
			&& receiveBuffer[i + 1] == uuidSeparator[1]
			&& receiveBuffer[i + 2] == uuidSeparator[2]
			&& receiveBuffer[i + 3] == uuidSeparator[3]
			&& receiveBuffer[i + 4] == uuidSeparator[4]
			&& receiveBuffer[i + 5] == uuidSeparator[5]) {
			// UUID starts after query string in https://hack.gt?user=<uuid>
			i += 5;
			isUUIDSection = true;
			continue;
		}
		if (isUUIDSection) {
			message.payload[uuidIndex] = receiveBuffer[i];
			uuidIndex++;
		}
	}

	mfrc522.PICC_HaltA();  // Stop reading

	if (!isUUIDSection) {
		failure();
		delay(150);
		failure();

		#ifdef DEBUG
			Serial.println(F("No UUID found on tapped badge"));
		#endif
		return;
	}

	success();

	bool sendSuccess = radio.sendWithRetry(BASE_STATION_ID, (const void*)(&message), sizeof(Message), RETRY_COUNT, ACK_TIMEOUT);
	if (!sendSuccess) {
		failure();
		#ifdef DEBUG
			Serial.print(F("Got no ACK for UUID: "));
			Serial.println((char*)message.payload);
		#endif
		return;
	}

	#ifdef DEBUG
		Serial.print(F("Sent UUID: "));
		Serial.println((char*)message.payload);
	#endif
}

void success() {
	digitalWrite(GREEN, HIGH);
	tone(BUZZER, 1000);
	delay(250);
	noTone(BUZZER);
	digitalWrite(GREEN, LOW);
}
void failure() {
	digitalWrite(RED, HIGH);
	tone(BUZZER, 300);
	delay(250);
	noTone(BUZZER);
	digitalWrite(RED, LOW);
}

void hexPrint(byte* buff, byte buffSize) {
    for (byte i = 0; i < buffSize; i++) {
        if (i % 4 == 0)
            Serial.println();

        if (buff[i] < 0x10)
            Serial.print("0");
        Serial.print(buff[i], HEX);
        Serial.print(" ");
    }
    Serial.println();
}
